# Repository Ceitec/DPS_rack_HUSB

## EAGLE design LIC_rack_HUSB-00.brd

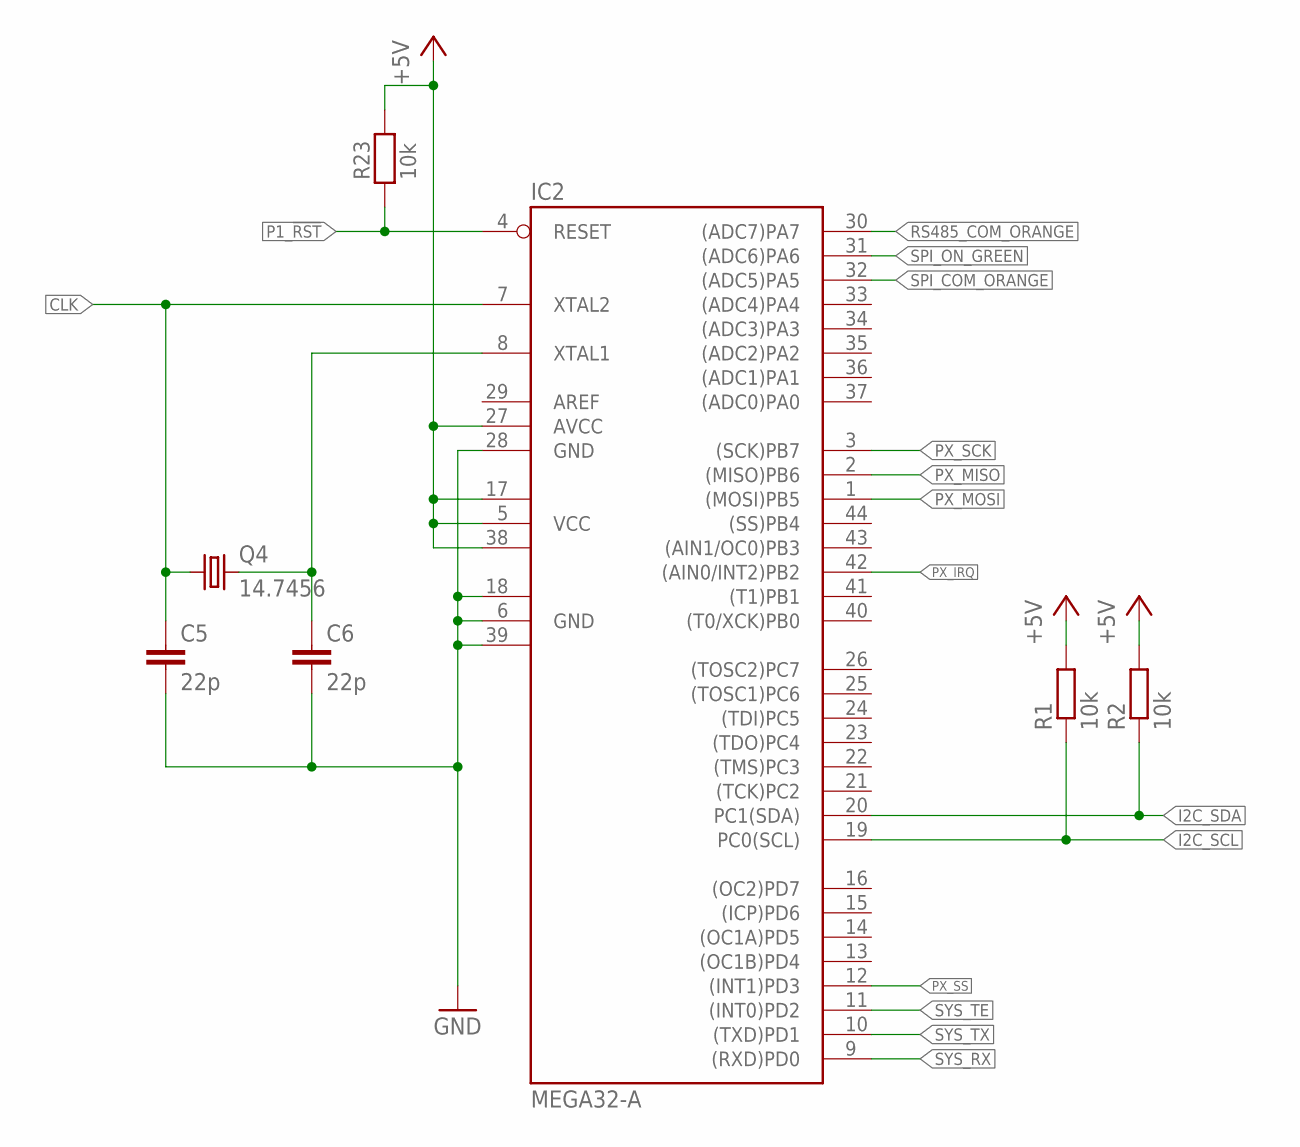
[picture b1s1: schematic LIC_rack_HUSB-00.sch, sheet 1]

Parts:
C5, C6: 22p; C0805
IC2: MEGA32-A; TQFP44
Q4: 14.7456; HC49U70
R1, R2: 10k; R1206
R23: 10k; 1206

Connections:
+5V: IC2.5 (VCC), IC2.17 (VCC1), IC2.27 (AVCC), IC2.38 (VCC2), R1.2, R2.2, R23.2; also elsewhere on the board
CLK: C5.1, IC2.7 (XTAL2), Q4.1
GND: C5.2, C6.2, IC2.6 (GND), IC2.18 (GND1), IC2.28 (GND), IC2.39 (GND2); also elsewhere on the board
I2C_SCL: IC2.19 (PC0(SCL)), R1.1
I2C_SDA: IC2.20 (PC1(SDA)), R2.1
unnamed: C6.1, IC2.8 (XTAL1), Q4.2
P1_!RST: IC2.4 (RESET), R23.1; also elsewhere on the board
PX_IRQ: IC2.42 ((AIN0/INT2)PB2)
PX_MISO: IC2.2 ((MISO)PB6); also elsewhere on the board
PX_MOSI: IC2.1 ((MOSI)PB5); also elsewhere on the board
PX_SCK: IC2.3 ((SCK)PB7); also elsewhere on the board
PX_SS: IC2.12 ((INT1)PD3)
RS485_COM_ORANGE: IC2.30 ((ADC7)PA7); also elsewhere on the board
SPI_COM_ORANGE: IC2.32 ((ADC5)PA5); also elsewhere on the board
SPI_ON_GREEN: IC2.31 ((ADC6)PA6); also elsewhere on the board
SYS_RX: IC2.9 ((RXD)PD0); also elsewhere on the board
SYS_TE: IC2.11 ((INT0)PD2); also elsewhere on the board
SYS_TX: IC2.10 ((TXD)PD1); also elsewhere on the board

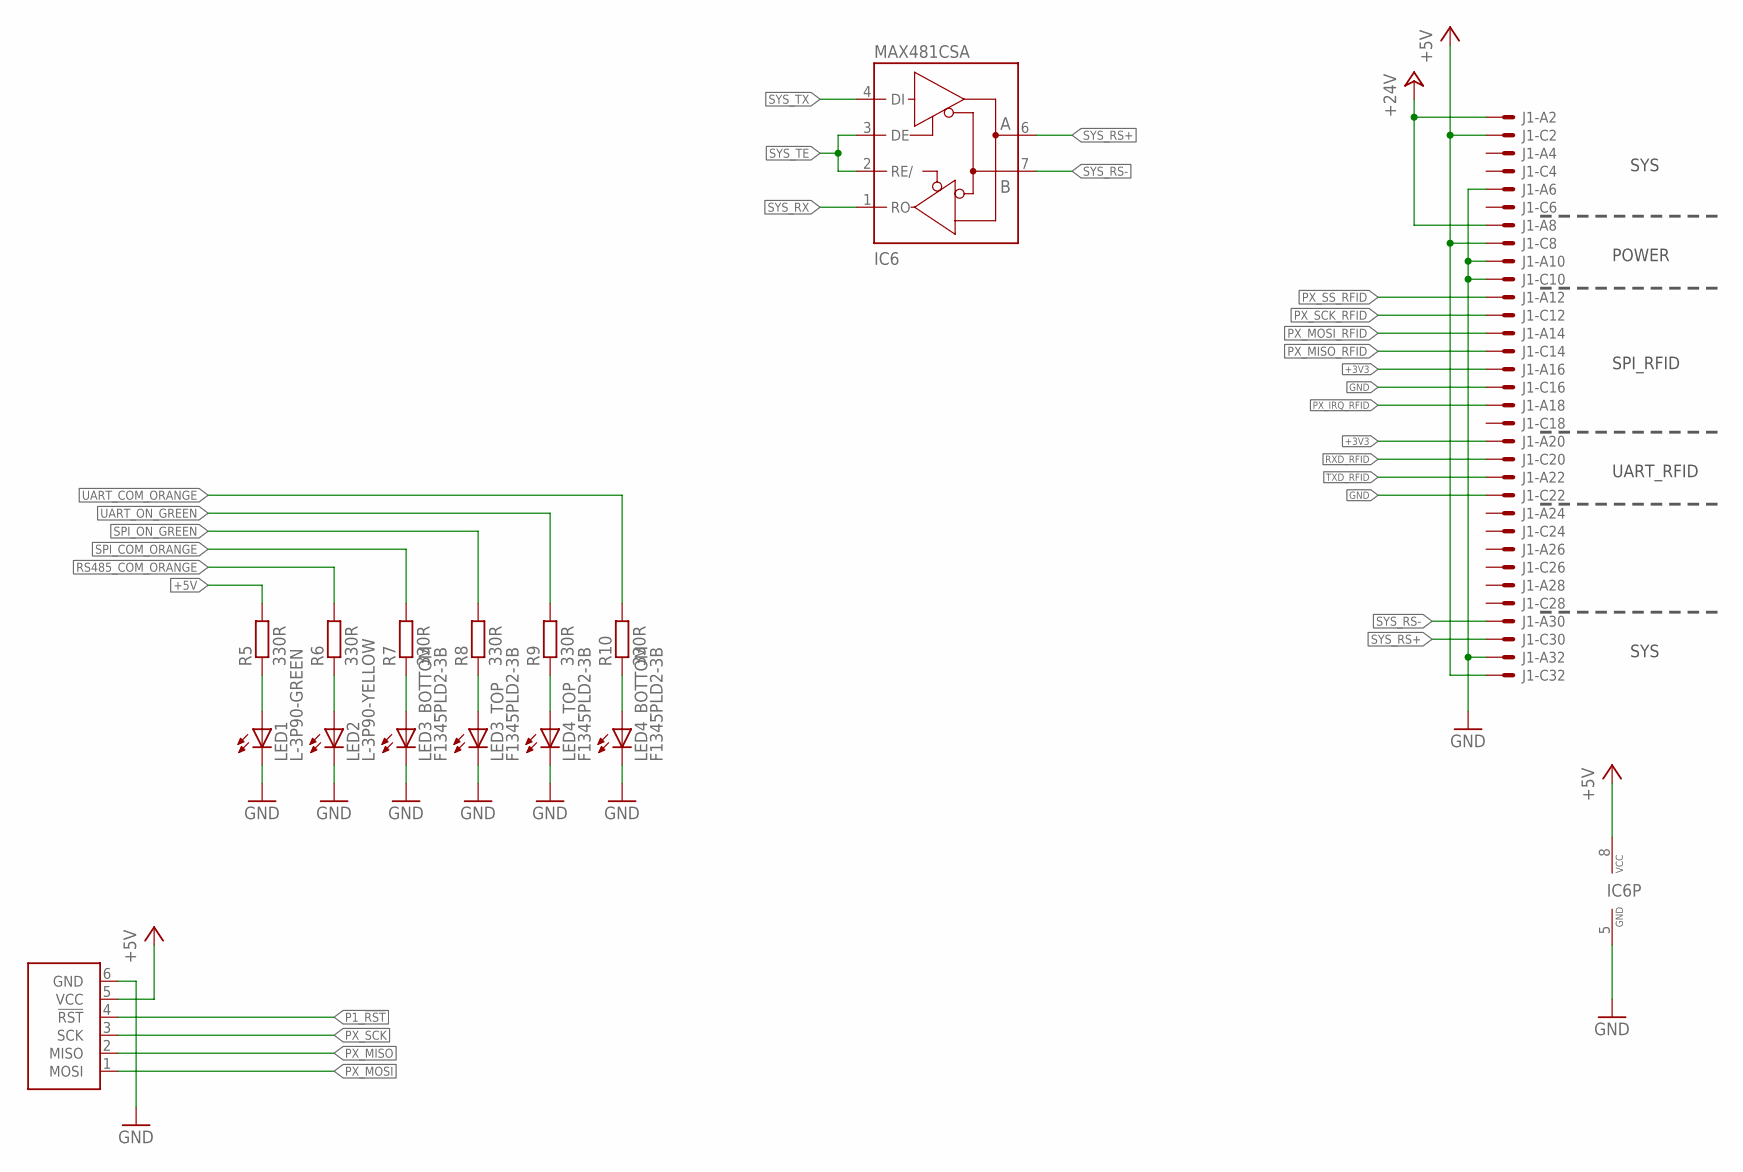
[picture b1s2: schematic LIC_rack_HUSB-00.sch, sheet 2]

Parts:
IC6: MAX481CSA; SO08
J1: VG32SP; VG32P
LED1: L-3P90-GREEN; L-3P90
LED2: L-3P90-YELLOW; L-3P90
LED3, LED4: F1345PLD2-3B
R5, R6, R7, R8, R9, R10: 330R; R1206
U1: ATPROG-V; 6410-06

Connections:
+3V3: J1.A16 (MS), J1.A20 (MS)
+5V: IC6.8 (VCC), J1.C2 (MS), J1.C8 (MS), J1.C32 (MSV), R5.2, U1.5 (VCC); also elsewhere on the board
+24V: J1.A2 (MS), J1.A8 (MS)
GND: IC6.5 (GND), J1.A6 (MS), J1.A10 (MS), J1.A32 (MS), J1.C10 (MS), J1.C16 (MS), J1.C22 (MS), LED1.K (C), LED2.K (C), LED3.1K (C), LED3.2K (C), LED4.1K (C), LED4.2K (C), U1.6 (GND); also elsewhere on the board
unnamed: LED2.A, R6.1
unnamed: LED1.A, R5.1
unnamed: LED4.1A (A), R10.1
unnamed: LED4.2A (A), R9.1
unnamed: LED3.2A (A), R8.1
unnamed: LED3.1A (A), R7.1
P1_!RST: U1.4 (!RST); also elsewhere on the board
PX_IRQ_RFID: J1.A18 (MS)
PX_MISO: U1.2 (MISO); also elsewhere on the board
PX_MISO_RFID: J1.C14 (MS)
PX_MOSI: U1.1 (MOSI); also elsewhere on the board
PX_MOSI_RFID: J1.A14 (MS)
PX_SCK: U1.3 (SCK); also elsewhere on the board
PX_SCK_RFID: J1.C12 (MS)
PX_SS_RFID: J1.A12 (MS)
RS485_COM_ORANGE: R6.2; also elsewhere on the board
RXD_RFID: J1.C20 (MS)
SPI_COM_ORANGE: R7.2; also elsewhere on the board
SPI_ON_GREEN: R8.2; also elsewhere on the board
SYS_RS+: IC6.6 (A), J1.C30 (MS)
SYS_RS-: IC6.7 (B), J1.A30 (MS)
SYS_RX: IC6.1 (RO); also elsewhere on the board
SYS_TE: IC6.2 (RE/), IC6.3 (DE); also elsewhere on the board
SYS_TX: IC6.4 (DI); also elsewhere on the board
TXD_RFID: J1.A22 (MS)
UART_COM_ORANGE: R10.2
UART_ON_GREEN: R9.2

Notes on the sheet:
SYS
POWER
SPI_RFID
UART_RFID

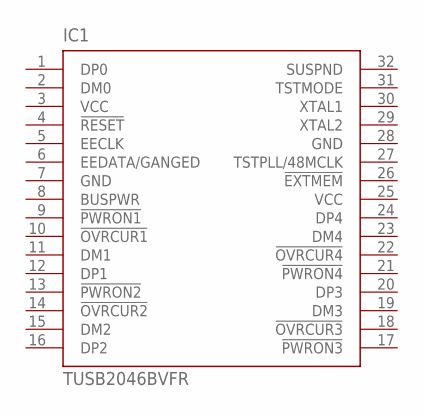
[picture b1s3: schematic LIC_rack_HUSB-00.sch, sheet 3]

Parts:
IC1: TUSB2046BVFR; VF_S-PQFP-G32

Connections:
GND: IC1.7 (GND), IC1.28 (GND); also elsewhere on the board
VCC: IC1.3 (VCC), IC1.25 (VCC)

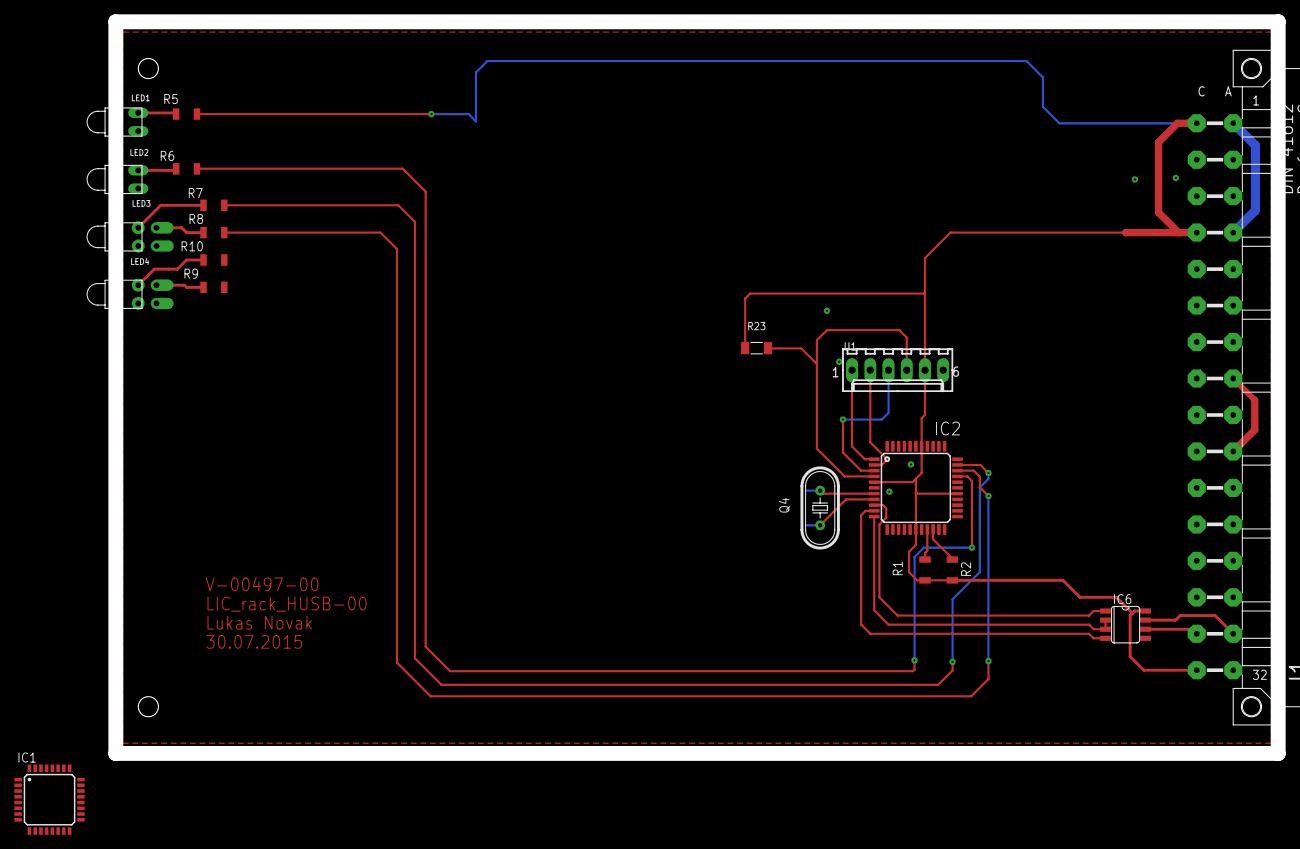
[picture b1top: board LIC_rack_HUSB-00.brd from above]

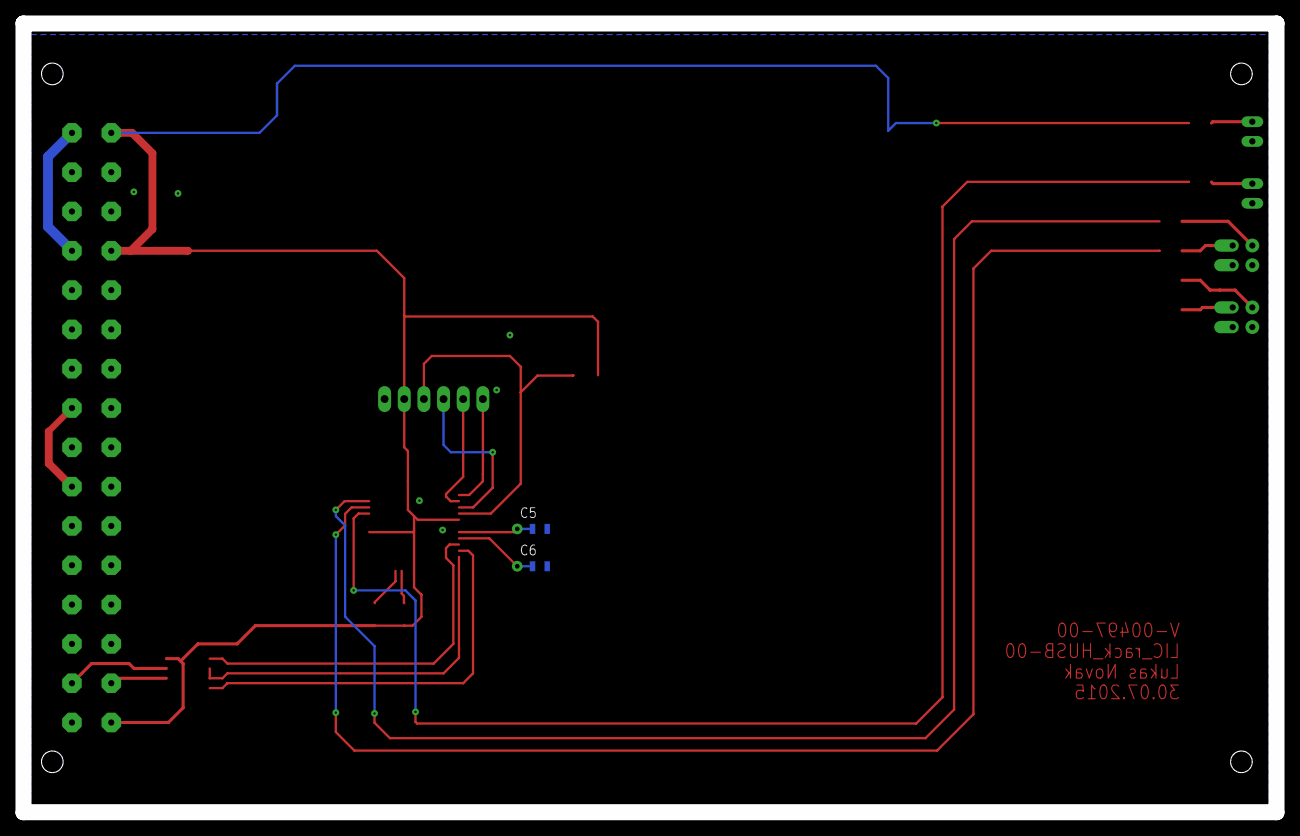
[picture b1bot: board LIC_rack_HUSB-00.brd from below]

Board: 2 copper layers, 162.0 x 102.0 mm, 21 parts (2 on the bottom side), 27 nets.

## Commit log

2015-08-11 :neckbeard: Added .gitattributes & .gitignore files
2015-08-11 Hub USB
    Hub USB do Euro Karty
2015-09-25 A
    A

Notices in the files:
parts and their libraries:
Copyright (C) PaJa 2001-2014
